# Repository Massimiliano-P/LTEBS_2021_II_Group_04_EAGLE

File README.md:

# LTEBS_2021_II_Group_04_EAGLE
The repository contains Eagle files required for the design of a testing PCB embedding a development kit for the PSoC 5LP (CY8CKIT-059) and other components connected to it. 

## Library
It contains a library containing two custom components

## Project
It contains two files with the schematic and the board design respectively

## Design rules
It contains a file with the design rules provided by the manufacturer (MDSrl)

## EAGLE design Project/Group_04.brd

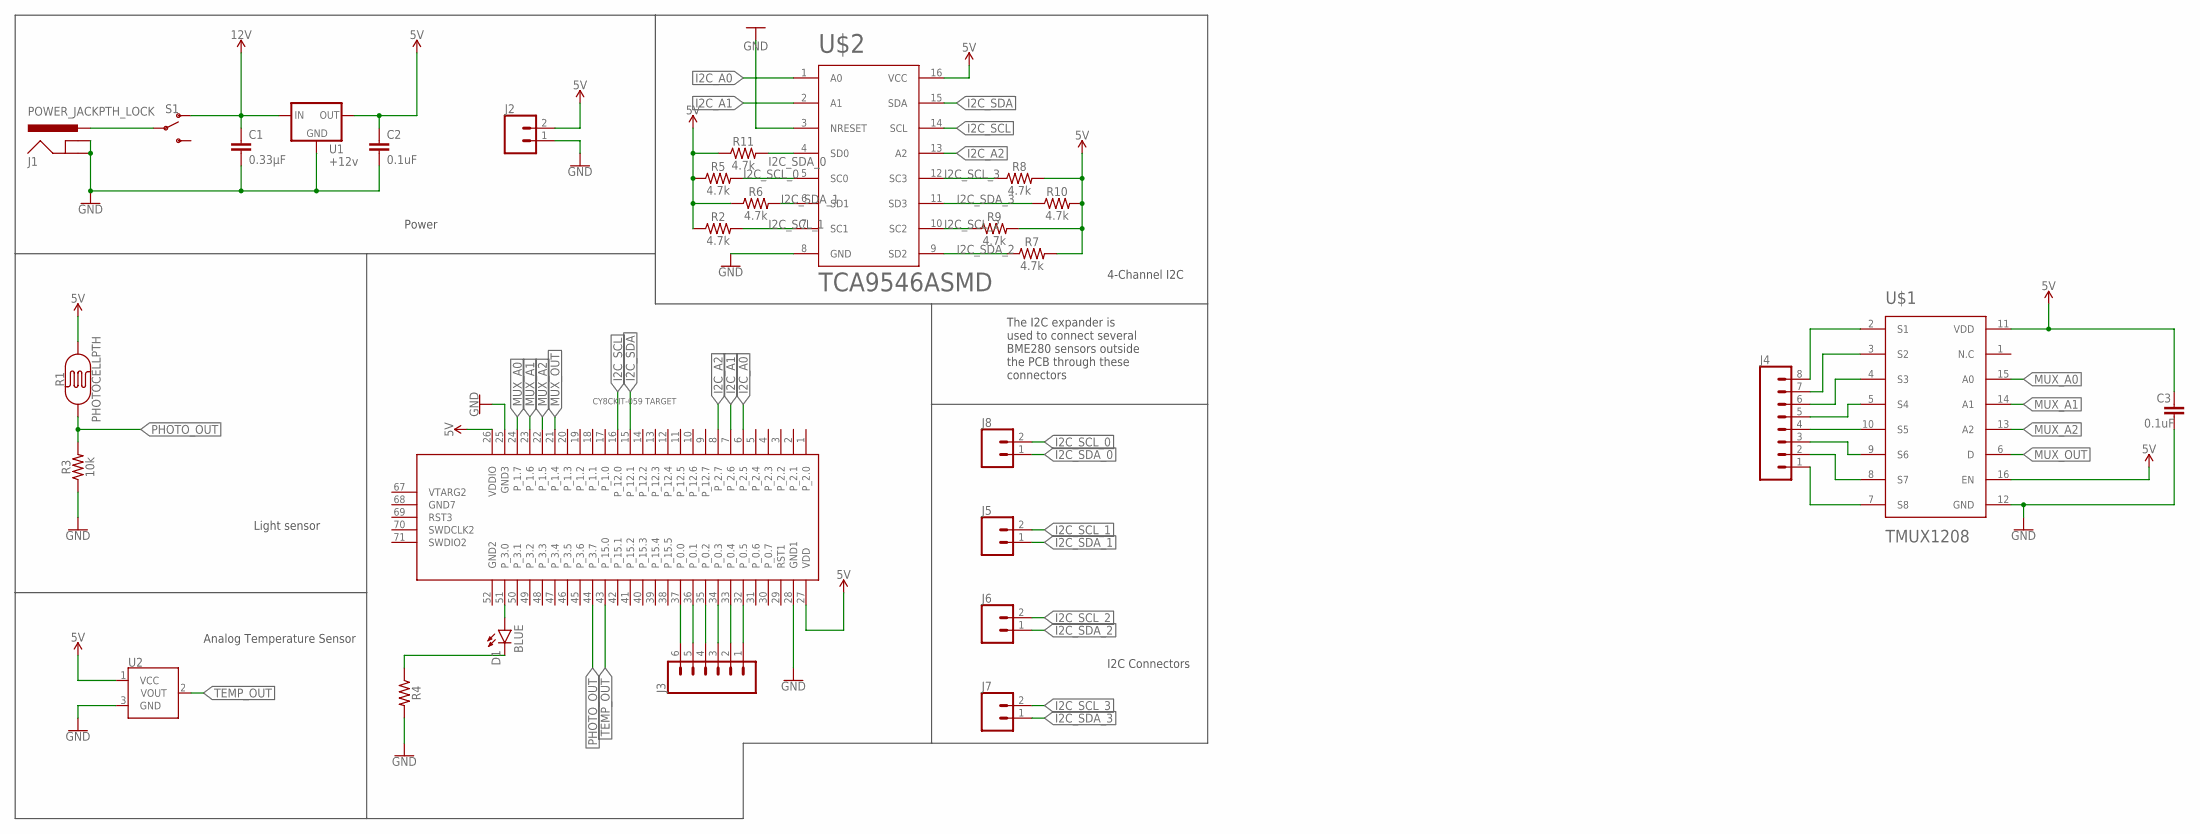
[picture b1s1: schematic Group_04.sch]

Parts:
C1: 0.33µF; 0805
C2, C3: 0.1uF; CAP-PTH-SMALL-KIT
D1: BLUE; LED-1206
J1: POWER_JACKPTH_LOCK; POWER_JACK_PTH_LOCK
J2, J5, J6, J7, J8: CONN_02; 1X02
J3: CONN_06LOCK; 1X06_LOCK
J4: CONN_08LOCK; 1X08_LOCK
R1: PHOTOCELLPTH; PHOTOCELL
R2, R5, R6, R7, R8, R9, R10, R11: 4.7k; 0603
R3: 10k; 0603
R4: AXIAL-0.3
S1: SWITCH-SPDT-PTH-11.6X4.0MM; SWITCH_SPDT_PTH_11.6X4.0MM
U1: +12v; TO-252
U2: TMP36GT9; TO-92
U$1: TMUX1208; QFN-16
U$2: TCA9546ASMD; TSSOP-16
U$3: CY8CKIT-059_TARGET

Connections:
5V: C2.1, C3.1, J2.2, R1.2, R2.1, R5.1, R6.1, R7.2, R8.2, R9.2, R10.2, R11.1, U1.2 (OUT), U2.1 (VCC), U$1.11 (VDD), U$1.16 (EN), U$2.16 (VCC), U$3.26 (VDDIO), U$3.27 (VDD)
12V: C1.1, S1.1 (O), U1.1 (IN)
GND: C1.2, C2.2, C3.2, J1.GND, J1.GNDBREAK, J2.1, R3.1, R4.P$2 (2), U1.3 (GND), U2.3 (GND), U$1.12 (GND), U$2.3 (NRESET), U$2.8 (GND), U$3.25 (GND3), U$3.28 (GND1)
I2C_A0: U$2.1 (A0), U$3.6 (P_2.5)
I2C_A1: U$2.2 (A1), U$3.7 (P_2.6)
I2C_A2: U$2.13 (A2), U$3.8 (P_2.7)
I2C_SCL: U$2.14 (SCL), U$3.16 (P_12.0)
I2C_SCL_0: J8.2, R5.2, U$2.5 (SC0)
I2C_SCL_1: J5.2, R2.2, U$2.7 (SC1)
I2C_SCL_2: J6.2, R9.1, U$2.10 (SC2)
I2C_SCL_3: J7.2, R8.1, U$2.12 (SC3)
I2C_SDA: U$2.15 (SDA), U$3.15 (P_12.1)
I2C_SDA_0: J8.1, R11.2, U$2.4 (SD0)
I2C_SDA_1: J5.1, R6.2, U$2.6 (SD1)
I2C_SDA_2: J6.1, R7.1, U$2.9 (SD2)
I2C_SDA_3: J7.1, R10.1, U$2.11 (SD3)
MUX_A0: U$1.15 (A0), U$3.24 (P_1.7)
MUX_A1: U$1.14 (A1), U$3.23 (P_1.6)
MUX_A2: U$1.13 (A2), U$3.22 (P_1.5)
MUX_OUT: U$1.6 (D), U$3.21 (P_1.4)
unnamed: J1.PWR, S1.2
unnamed: J4.4, U$1.10 (S5)
unnamed: J4.8, U$1.2 (S1)
unnamed: J4.7, U$1.3 (S2)
unnamed: J4.6, U$1.4 (S3)
unnamed: J4.5, U$1.5 (S4)
unnamed: J4.3, U$1.9 (S6)
unnamed: J4.2, U$1.8 (S7)
unnamed: J4.1, U$1.7 (S8)
unnamed: D1.C, R4.P$1 (1)
unnamed: D1.A, U$3.51 (P_3.0)
unnamed: J3.6, U$3.37 (P_0.0)
unnamed: J3.5, U$3.36 (P_0.1)
unnamed: J3.4, U$3.35 (P_0.2)
unnamed: J3.3, U$3.34 (P_0.3)
unnamed: J3.2, U$3.33 (P_0.4)
unnamed: J3.1, U$3.32 (P_0.5)
PHOTO_OUT: R1.1, R3.2, U$3.44 (P_3.7)
TEMP_OUT: U2.2 (VOUT), U$3.43 (P_15.0)

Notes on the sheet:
The I2C expander is used to connect several BME280 sensors outside the PCB through these connectors
4-Channel I2C
Power
Light sensor
Analog Temperature Sensor
I2C Connectors

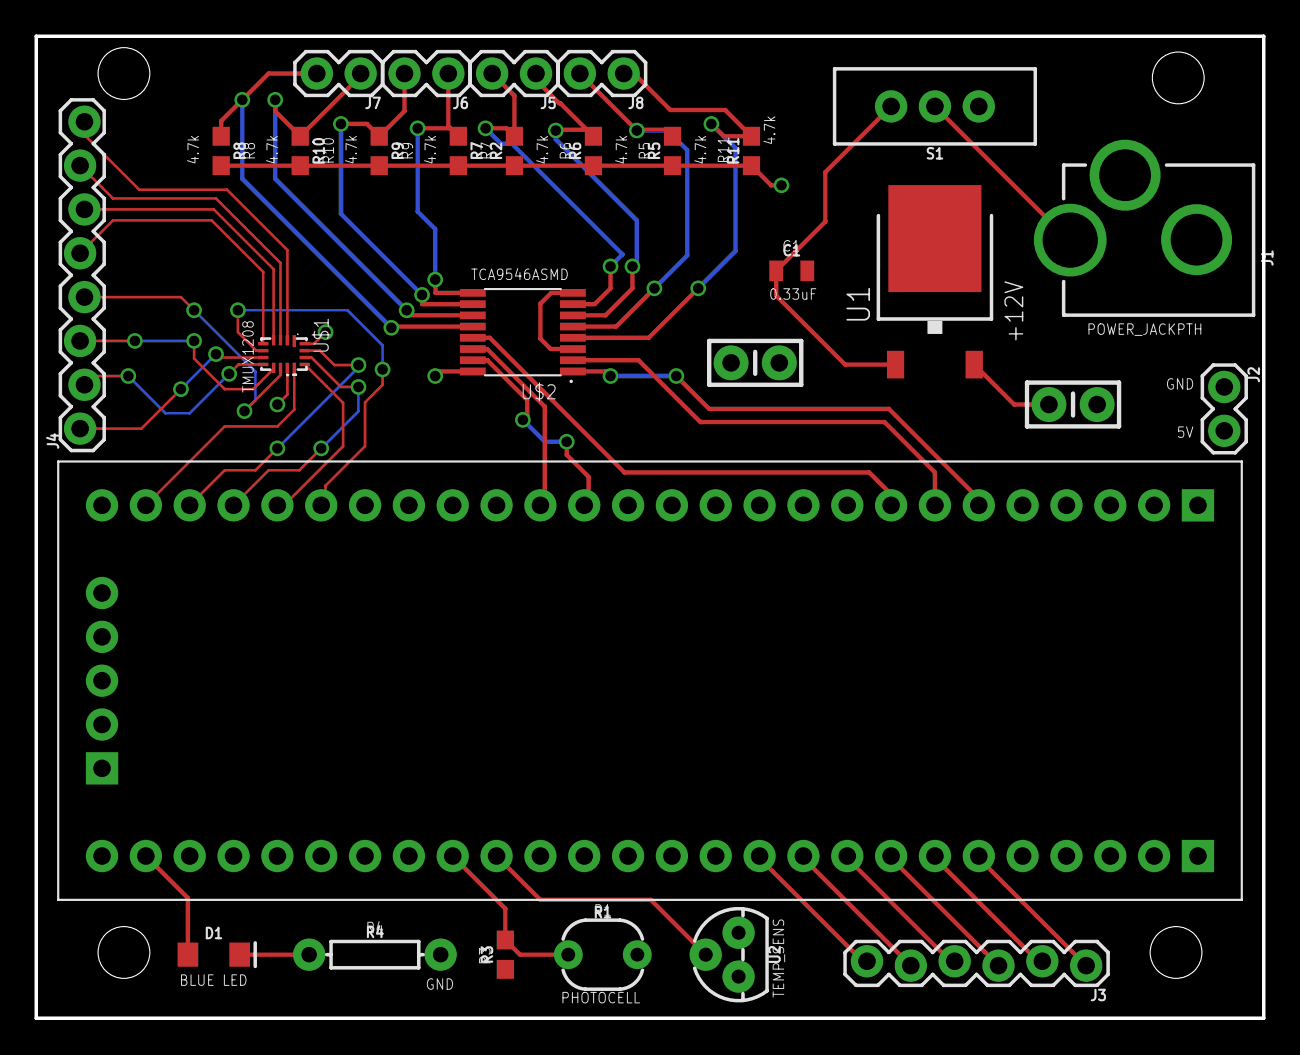
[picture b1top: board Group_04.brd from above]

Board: 2 copper layers, 71.1 x 56.9 mm, 29 parts (0 on the bottom side), 39 nets.

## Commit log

2021-03-19 schematic and library
2021-03-19 added frame
2021-03-20 modified frame and fixed component
2021-03-21 fixed error on 5V pin
2021-03-22 fixed mux connections
2021-03-22 library modified
2021-03-22 fixed mux component schematic
2021-03-22 board created
2021-03-22 components are positioned
2021-03-22 routed
2021-03-22 copper pour added
2021-03-23 V5,GND copper pours modified and PCB scaled down
2021-03-24 one warning fixed, silkscreen and dru file
2021-03-24 copper pour modified, power jack re-oriented
2021-03-24 adjusted wire warning
2021-03-24 added silkscreen
2021-03-25 warnings solved, some vias resized
2021-03-25 dimension fixed
2021-03-26 fixed design rules
2021-03-26 modified gitignore
2021-03-26 fixed dimension
2021-03-26 Final version

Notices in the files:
parts and their libraries:
SparkFun-Capacitors: Licensing: Creative Commons ShareAlike 4.0 International - https://creativecommons.org/licenses/by-sa/4.0
